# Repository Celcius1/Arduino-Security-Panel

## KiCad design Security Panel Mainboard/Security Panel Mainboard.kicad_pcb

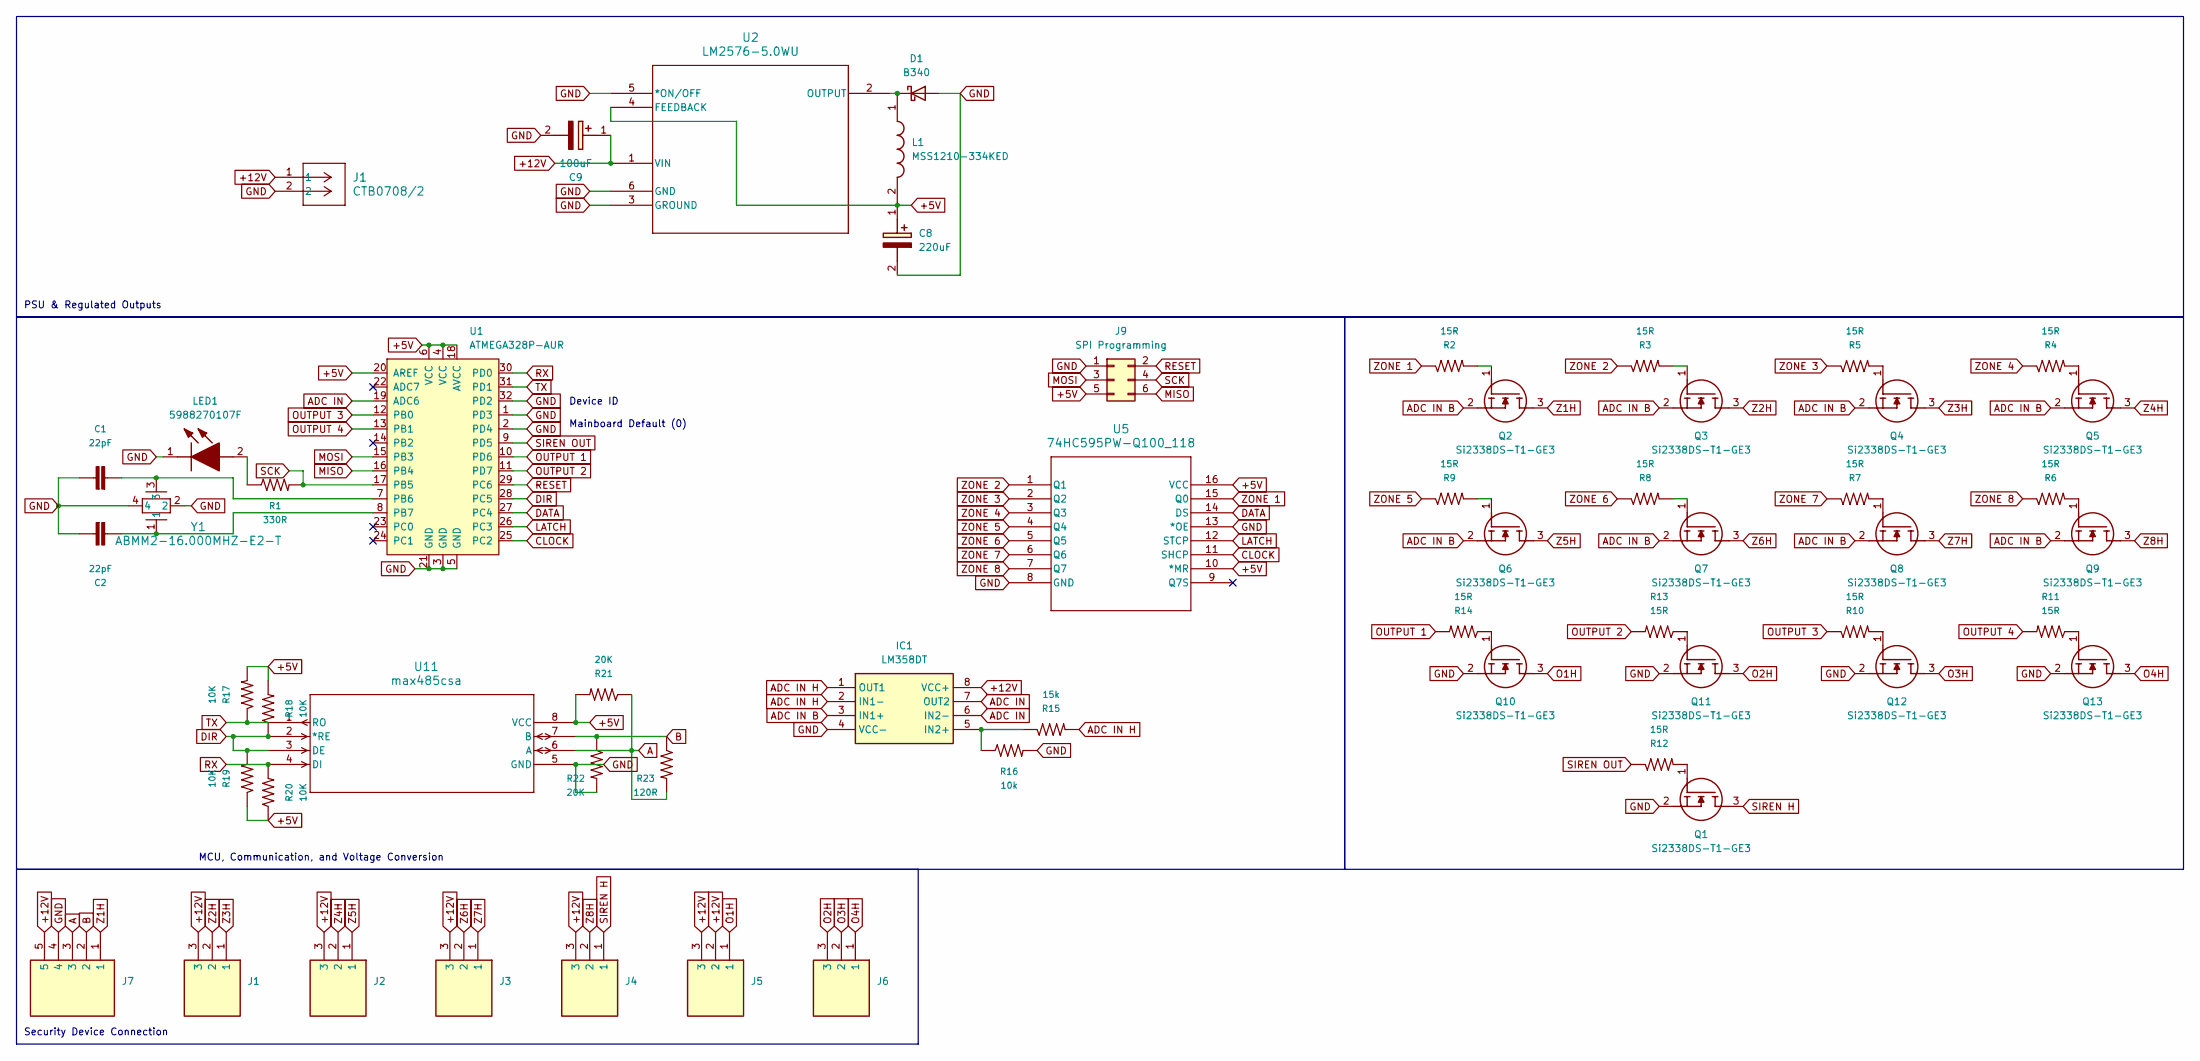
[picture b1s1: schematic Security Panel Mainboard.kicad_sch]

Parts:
C1, C2: 22pF; C_0805_2012Metric_Pad1.18x1.45mm_HandSolder
C8: 220uF; EEE0JA152UAP; Manufacturer_Part_Number EEEFK1H221P
C9: 100uF; CAPAE1050X1250N; Manufacturer_Part_Number MAL214699104E3
D1: B340; D_SMC
IC1: LM358DT; SOIC127P600X175-8N; Manufacturer_Part_Number LM358DT
J1: CTB0708/2; CONN-2X1_CTB0708&slash_2_CMD
J2, J3, J4, J5, J6: CTB0508_3; CTB05083; Manufacturer_Part_Number CTB0508/3
J7: CTB0508_5; CTB05085; Manufacturer_Part_Number CTB0508/5
J9: SPI Programming; PinHeader_2x03_P2.54mm_Vertical
L1: MSS1210-334KED; INDPM123123X1020N; Manufacturer_Part_Number MSS1210-334KED
LED1: 5988270107F; Manufacturer_Part_Number 5988270107F
Q1, Q2, Q3, Q4, Q5, Q6, Q7, Q8, Q9, Q10, Q11, Q12, Q13: Si2338DS-T1-GE3; SOT95P237X112-3N; Manufacturer_Part_Number Si2338DS-T1-GE3
R1: 330R; R_0805_2012Metric_Pad1.20x1.40mm_HandSolder
R2, R3, R4, R5, R6, R7, R8, R9, R10, R11, R12, R13, R14: 15R; R_0805_2012Metric_Pad1.20x1.40mm_HandSolder
R15: 15k; R_0805_2012Metric_Pad1.20x1.40mm_HandSolder
R16: 10k; R_0805_2012Metric_Pad1.20x1.40mm_HandSolder
R17, R18, R19, R20: 10K; R_0805_2012Metric_Pad1.20x1.40mm_HandSolder
R21, R22: 20K; R_0805_2012Metric_Pad1.20x1.40mm_HandSolder
R23: 120R; R_0805_2012Metric_Pad1.20x1.40mm_HandSolder
U1: ATMEGA328P-AUR; TQFP-32_7x7mm; MPN ATMEGA328P-AUR; Digi-Key_PN ATMEGA328P-AURCT-ND
U2: LM2576-5.0WU; TO-263-5_U_MCH
U5: 74HC595PW-Q100_118; 74HC595PW-Q100_118_NEX
U11: max485csa; 21-0041B_8_MXM
Y1: ABMM2-16.000MHZ-E2-T; CRYSTAL_ABMM2_ABR

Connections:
+5V: C8.1 (+), J9.5, L1.2, R17.2, R18.2, R19.1, R20.1, R21.2, U1.4 (VCC), U1.6 (VCC), U1.18 (AVCC), U1.20 (AREF), U2.4 (FEEDBACK), U5.10 (*MR), U5.16 (VCC), U11.8 (VCC)
A: J7.3, R21.1, R23.2, U11.6 (A)
ADC IN: IC1.6 (IN2-), IC1.7 (OUT2), U1.19 (ADC6)
ADC IN B: IC1.3 (IN1+), Q2.2 (S), Q3.2 (S), Q4.2 (S), Q5.2 (S), Q6.2 (S), Q7.2 (S), Q8.2 (S), Q9.2 (S)
ADC IN H: IC1.1 (OUT1), IC1.2 (IN1-), R15.2
B: J7.2, R22.1, R23.1, U11.7 (B)
CLOCK: U1.25 (PC2), U5.11 (SHCP)
DATA: U1.27 (PC4), U5.14 (DS)
DIR: R18.1, R19.2, U1.28 (PC5), U11.2 (*RE), U11.3 (DE)
LATCH: U1.26 (PC3), U5.12 (STCP)
MISO: J9.6, U1.16 (PB4)
MOSI: J9.3, U1.15 (PB3)
unnamed: D1.1 (K), L1.1, U2.2 (OUTPUT)
unnamed: IC1.5 (IN2+), R15.1, R16.1
unnamed: LED1.2 (A), R1.1
unnamed: Q1.1 (G), R12.2
unnamed: Q2.1 (G), R2.2
unnamed: Q3.1 (G), R3.2
unnamed: Q4.1 (G), R5.2
unnamed: Q5.1 (G), R4.2
unnamed: Q6.1 (G), R9.2
unnamed: Q7.1 (G), R8.2
unnamed: Q8.1 (G), R7.2
unnamed: Q9.1 (G), R6.2
unnamed: Q10.1 (G), R14.1
unnamed: Q11.1 (G), R13.1
unnamed: Q12.1 (G), R10.2
unnamed: Q13.1 (G), R11.1
unnamed: C1.2, U1.7 (PB6), Y1.3
unnamed: C2.2, U1.8 (PB7), Y1.1
O1H: J5.1, Q10.3 (D)
O2H: J6.3, Q11.3 (D)
O3H: J6.2, Q12.3 (D)
O4H: J6.1, Q13.3 (D)
OUTPUT 1: R14.2, U1.10 (PD6)
OUTPUT 2: R13.2, U1.11 (PD7)
OUTPUT 3: R10.1, U1.12 (PB0)
OUTPUT 4: R11.2, U1.13 (PB1)
RESET: J9.2, U1.29 (PC6)
RX: R20.2, U1.30 (PD0), U11.4 (DI)
SCK: J9.4, R1.2, U1.17 (PB5)
SIREN H: J4.1, Q1.3 (D)
SIREN OUT: R12.1, U1.9 (PD5)
TX: R17.1, U1.31 (PD1), U11.1 (RO)
Z1H: J7.1, Q2.3 (D)
Z4H: J2.2, Q5.3 (D)
Z5H: J2.1, Q6.3 (D)
Z6H: J3.2, Q7.3 (D)
Z7H: J3.1, Q8.3 (D)
Z8H: J4.2, Q9.3 (D)
ZONE 1: R2.1, U5.15 (Q0)
ZONE 2: R3.1, U5.1 (Q1)
ZONE 3: R5.1, U5.2 (Q2)
ZONE 4: R4.1, U5.3 (Q3)
ZONE 5: R9.1, U5.4 (Q4)
ZONE 6: R8.1, U5.5 (Q5)
ZONE 7: R7.1, U5.6 (Q6)
ZONE 8: R6.1, U5.7 (Q7)

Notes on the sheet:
Device ID Mainboard Default (0)
PSU & Regulated Outputs
Security Device Connection
MCU, Communication, and Voltage Conversion

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
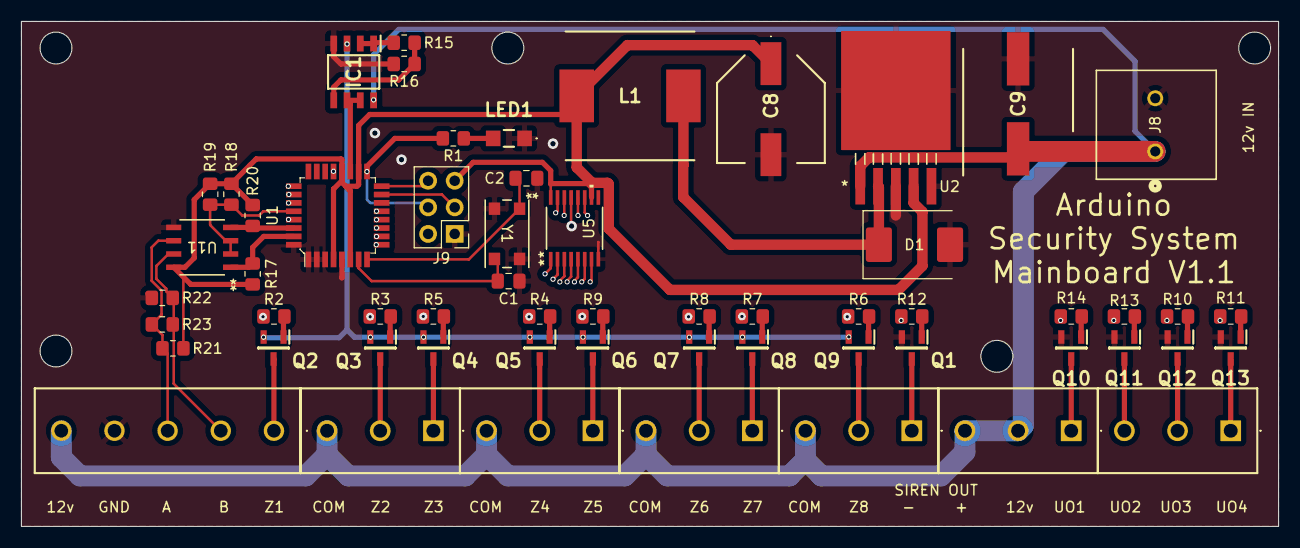
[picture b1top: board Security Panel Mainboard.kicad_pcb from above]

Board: 4 copper layers, 120.1 x 48.3 mm, 58 parts (0 on the bottom side), 62 nets.

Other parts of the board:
J8: CTB0708/2; CONN-2X1_CTB0708&slash_2_CMD

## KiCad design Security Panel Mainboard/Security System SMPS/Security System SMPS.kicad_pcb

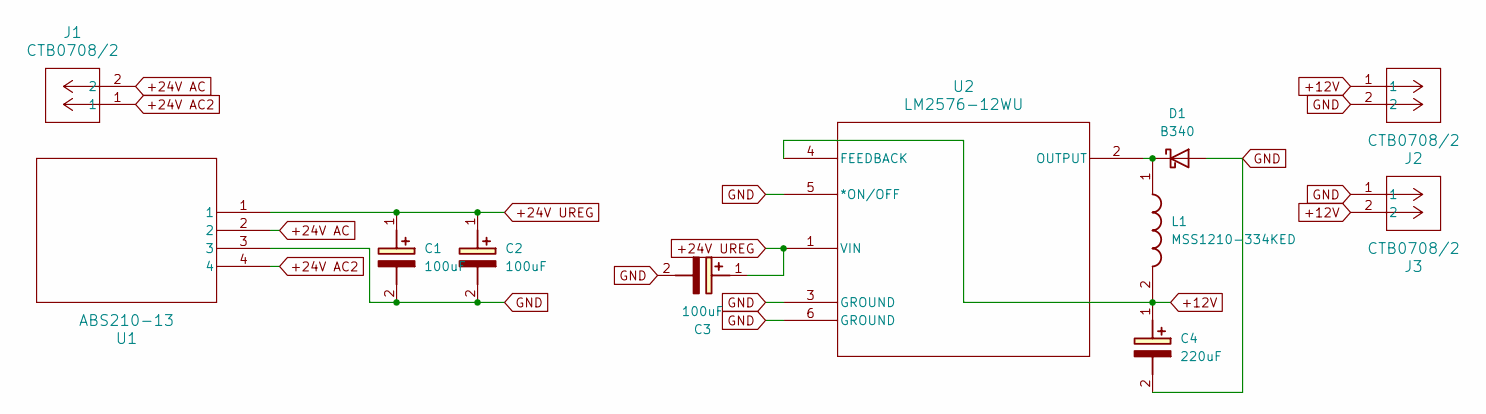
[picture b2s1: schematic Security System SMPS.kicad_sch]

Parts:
C1, C2, C3: 100uF; CAPAE1050X1250N; Manufacturer_Part_Number MAL214699104E3
C4: 220uF; EEE0JA152UAP; Manufacturer_Part_Number EEEFK1H221P
D1: B340; D_SMC
J1, J2, J3: CTB0708/2; CONN-2X1_CTB0708&slash_2_CMD
L1: MSS1210-334KED; INDPM123123X1020N; Manufacturer_Part_Number MSS1210-334KED
U1: ABS210-13; SON_S210-13_DIO
U2: LM2576-12WU; TO-263-5_U_MCH

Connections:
+12V: C4.1 (+), J2.1, J3.2, L1.2, U2.4 (FEEDBACK)
+24V AC: J1.2, U1.2
+24V AC2: J1.1, U1.4
+24V UREG: C1.1 (+), C2.1 (+), C3.1 (+), U1.1, U2.1 (VIN)
GND: C1.2 (-), C2.2 (-), C3.2 (-), C4.2 (-), D1.2 (A), J2.2, J3.1, U1.3, U2.3 (GROUND), U2.5 (*ON/OFF), U2.6 (GROUND)
unnamed: D1.1 (K), L1.1, U2.2 (OUTPUT)

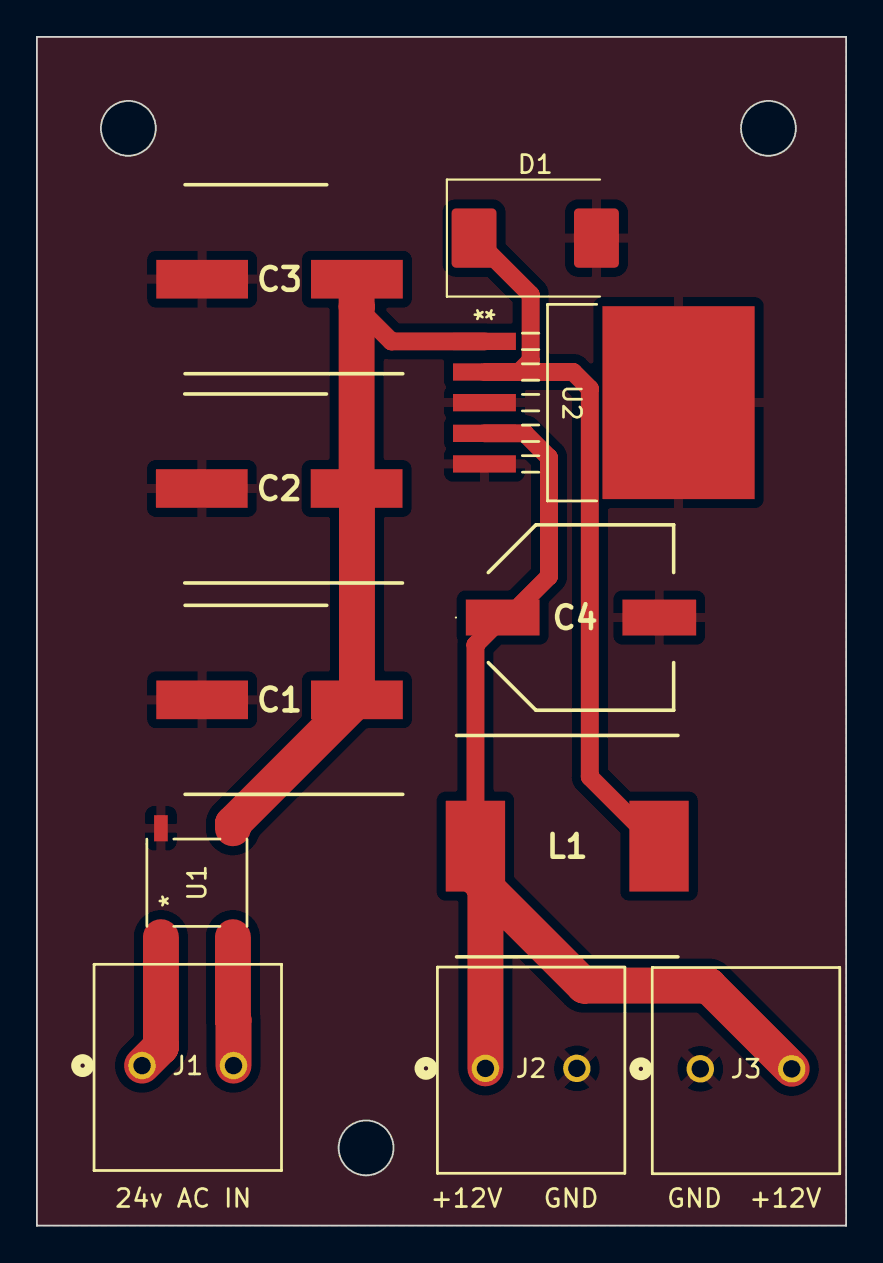
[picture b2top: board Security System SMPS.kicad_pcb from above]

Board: 2 copper layers, 45.0 x 66.0 mm, 11 parts (0 on the bottom side), 6 nets.

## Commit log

2025-01-03 Mainboard Design Complete
    Mainboard Designed and Gerbers generated
2025-01-05 Design Changes to PSU and Mainboard
